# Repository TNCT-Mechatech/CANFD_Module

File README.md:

# CANFD_Module
SPI->CAN FDに変換するモジュール

名前:ひなた
※画像は最新のものと比較すると古い部分があります．git pullして基板データを確認してください．
<br>

<br>

PCBAは[production/PCBA](production/PCBA)を参照してJLCPCBに発注してください．

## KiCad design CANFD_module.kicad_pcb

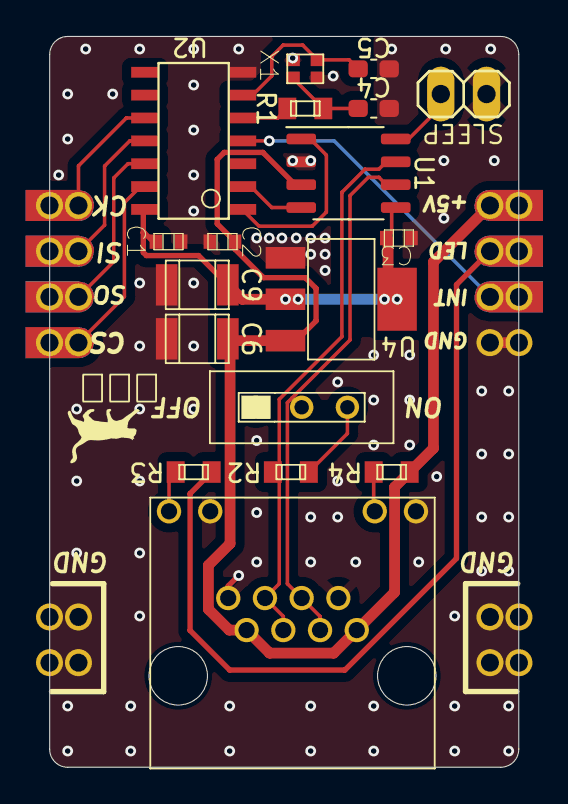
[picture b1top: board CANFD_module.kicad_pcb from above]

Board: 2 copper layers, 26.1 x 40.6 mm, 22 parts (0 on the bottom side), 20 nets.

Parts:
C1, C2, C3: GCM188L81H104KA57
C4, C5: GRM0225C1E6R0BA03L; C_0603_1608Metric_Pad1.08x0.95mm_HandSolder
C6, C9: GRM32ER71E226KE15; 3225M
JP2, JP3: PINHEAD(4)_RASPICO; 1X04
JP4, JP5: PINHEAD(2)_RASPICO; PINHEAD_2_RASPICO
R1: 0; CR0603
R2: 120Ω; CR0603
R3, R4: 150; CR0603
RJ45_1: MTJ-88ARX1-LH
SLEEP: PINHD-1X2; 1X02
SW1: SS-12SDP2
U1: MCP2558FD; SOP-8_3.9x4.9mm_P1.27mm
U2: MCP2517FD
U4: AZ1117CH-3.3TRG1; AZ1117C
X1: XRCGB40M000F4M01R0; XRCGB40M000F4M00R0

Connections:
+3V3: C1.P$1, C3.P$1, C9.L (1), U1.5 (VIO), U2.VDD, U4.OUTPUT, U4.VOUT (OUTPUT)
+5V: C2.P$1, C6.L (1), JP2.PIN1 (1), JP2.PIN1_ (1), R4.RIGHT, RJ45_1.1, RJ45_1.7, U1.3 (VDD), U4.INPUT
/CAN+: R2.RIGHT, RJ45_1.5, RJ45_1.6, U1.7 (CANH)
/CAN-: RJ45_1.3, RJ45_1.4, SW1.C, U1.6 (CANL)
/COM_LED: JP2.PIN2 (2), JP2.PIN2_ (2), R3.LEFT
/CS: JP3.PIN1 (1), JP3.PIN1_ (1), U2.NCS
/INT: JP2.PIN3 (3), JP2.PIN3_ (3), U2.INT
/MISO: JP3.PIN2 (2), JP3.PIN2_ (2), U2.SDO
/MOSI: JP3.PIN3 (3), JP3.PIN3_ (3), U2.SDI
/SCK: JP3.PIN4 (4), JP3.PIN4_ (4), U2.SCK
GND: C1.P$2, C2.P$2, C3.P$2, C4.2, C5.2, C6.R (2), C9.R (2), JP2.PIN4 (4), JP2.PIN4_ (4), JP4.PIN1 (1), JP4.PIN1_ (1), JP4.PIN2 (2), JP4.PIN2_ (2), JP5.PIN1 (1), JP5.PIN1_ (1), JP5.PIN2 (2), JP5.PIN2_ (2), RJ45_1.2, RJ45_1.8, RJ45_1.LED1_K, RJ45_1.LED2_K, SLEEP.1, U1.2 (VSS), U2.VSS, U4.GND, X1.NC1, X1.NC2
unnamed: C4.1, R1.RIGHT, X1.2
unnamed: C5.1, U2.OSC1, X1.1
unnamed: R1.LEFT, U2.OSC2
unnamed: R2.LEFT, SW1.R
unnamed: R3.RIGHT, RJ45_1.LED1_A
unnamed: R4.LEFT, RJ45_1.LED2_A
unnamed: U1.4 (RXD), U2.RXCAN
unnamed: SLEEP.2, U1.8 (S)
unnamed: U1.1 (TXD), U2.TXCAN

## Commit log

2023-03-29 途中まで
2023-03-29 Create license
2023-03-30 基板完成
2023-03-30 基板微修正
2023-10-22 [fix]0603->1608 package
2023-11-03 [fix]ピンアサインをver1.0と同じにした
2023-11-03 [fix]versionの表示
2023-11-15 [add]PCBA用のBOMを追加
2023-11-15 rm ignore files
2023-11-15 rm gerber files
